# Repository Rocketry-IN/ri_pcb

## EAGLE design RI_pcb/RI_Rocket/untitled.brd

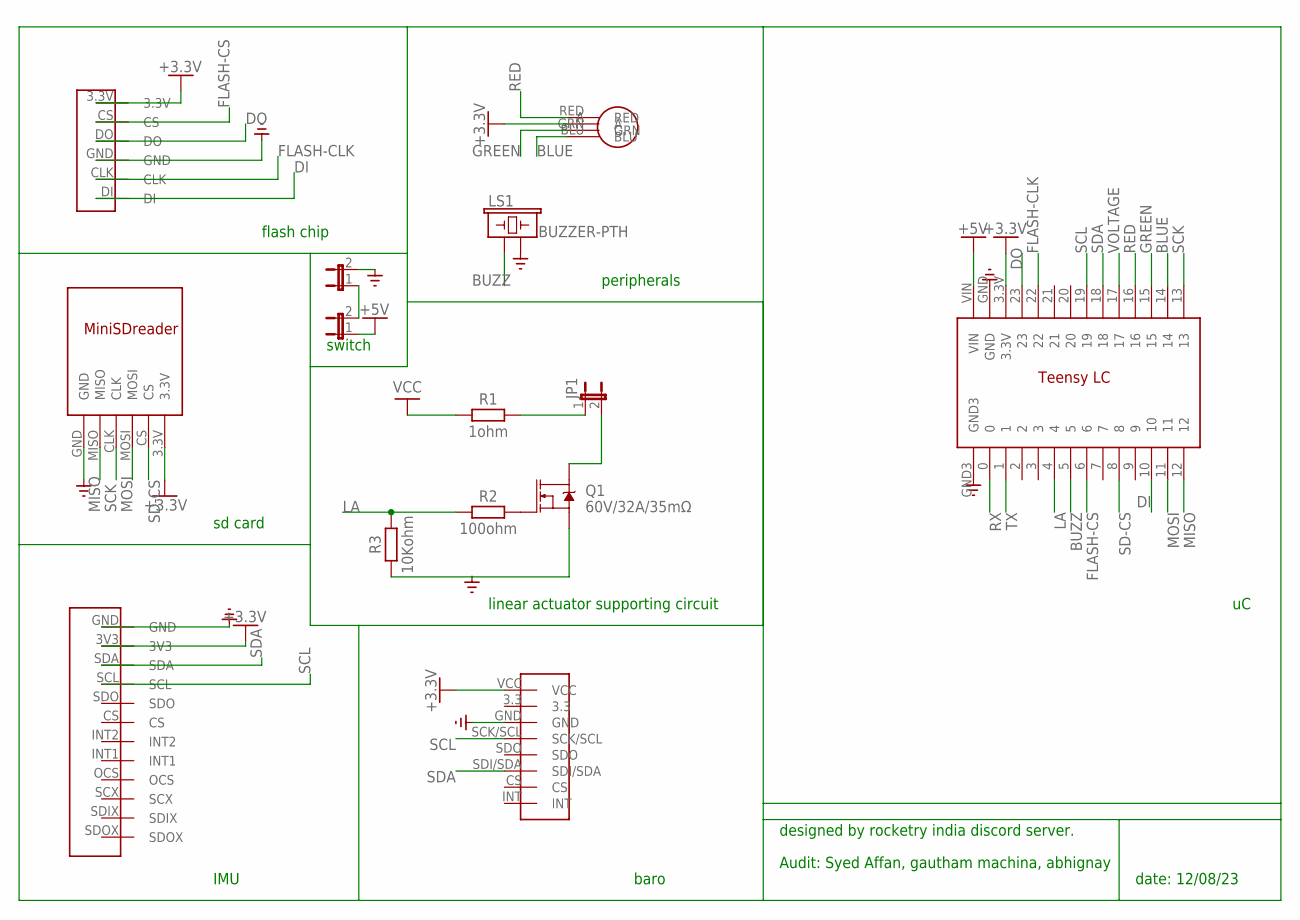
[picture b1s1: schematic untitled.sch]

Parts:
JP1, JP2, JP3: JP1E; JP1
LS1: BUZZER-PTH; BUZZER-12MM
Q1: 60V/32A/35mΩ; TO220V
R1: 1ohm; RESAD724W46L381D178B
R2: 100ohm; RESAD724W46L381D178B
R3: 10Kohm; RESAD724W46L381D178B
U$1: TEENSYLC
U$2: LED
U$3: FLASH
U$4: MINISDREADER
U$5: LSM6DSO
U$6: BMP390

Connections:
+3.3V: U$1.3.3V, U$2.A, U$3.3.3V, U$4.3.3V, U$5.3V3, U$6.VCC
+5V: JP3.1, U$1.VIN
BLUE: U$1.14, U$2.BLU
BUZZ: LS1.+ (1), U$1.5
DI: U$1.10, U$3.DI
DO: U$1.23, U$3.DO
FLASH-CLK: U$1.22, U$3.CLK
FLASH-CS: U$1.6, U$3.CS
GND: JP2.2, U$1.GND, U$3.GND, U$4.GND, U$5.GND, U$6.GND
GREEN: U$1.15, U$2.GRN
LA: R2.1, R3.2, U$1.4
MISO: U$1.12, U$4.MISO
MOSI: U$1.11, U$4.MOSI
unnamed: JP1.1, R1.2
unnamed: JP1.2, Q1.2 (D)
unnamed: Q1.1 (G), R2.2
unnamed: Q1.3 (S), R3.1
unnamed: JP2.1, JP3.2
RED: U$1.16, U$2.RED
RX: U$1.0
SCK: U$1.13, U$4.CLK
SCL: U$1.19, U$5.SCL, U$6.SCK/SCL
SD-CS: U$1.8, U$4.CS
SDA: U$1.18, U$5.SDA, U$6.SDI/SDA
TX: U$1.1
VCC: R1.1
VOLTAGE: U$1.17

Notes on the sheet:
designed by rocketry india discord server.
Audit: Syed Affan, gautham machina, abhignay
date: 12/08/23
switch
sd card
linear actuator supporting circuit
peripherals
IMU
baro
flash chip

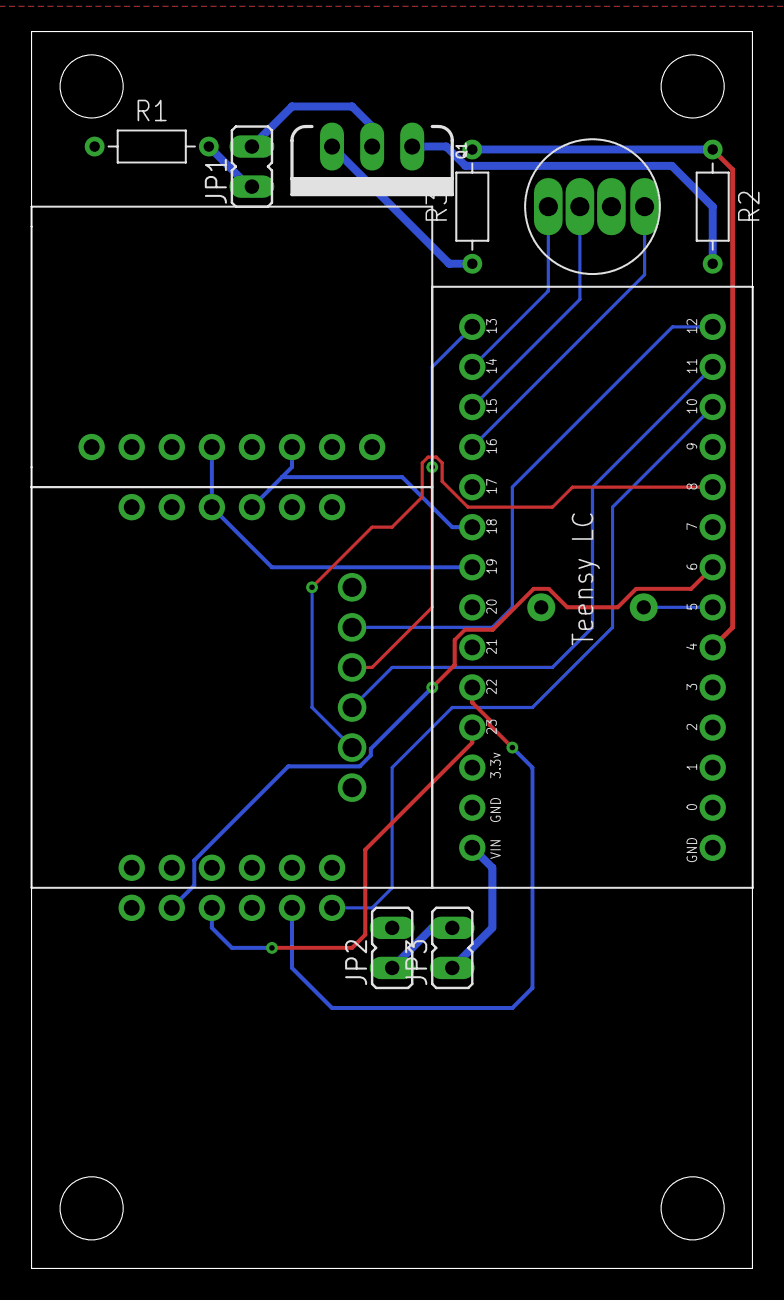
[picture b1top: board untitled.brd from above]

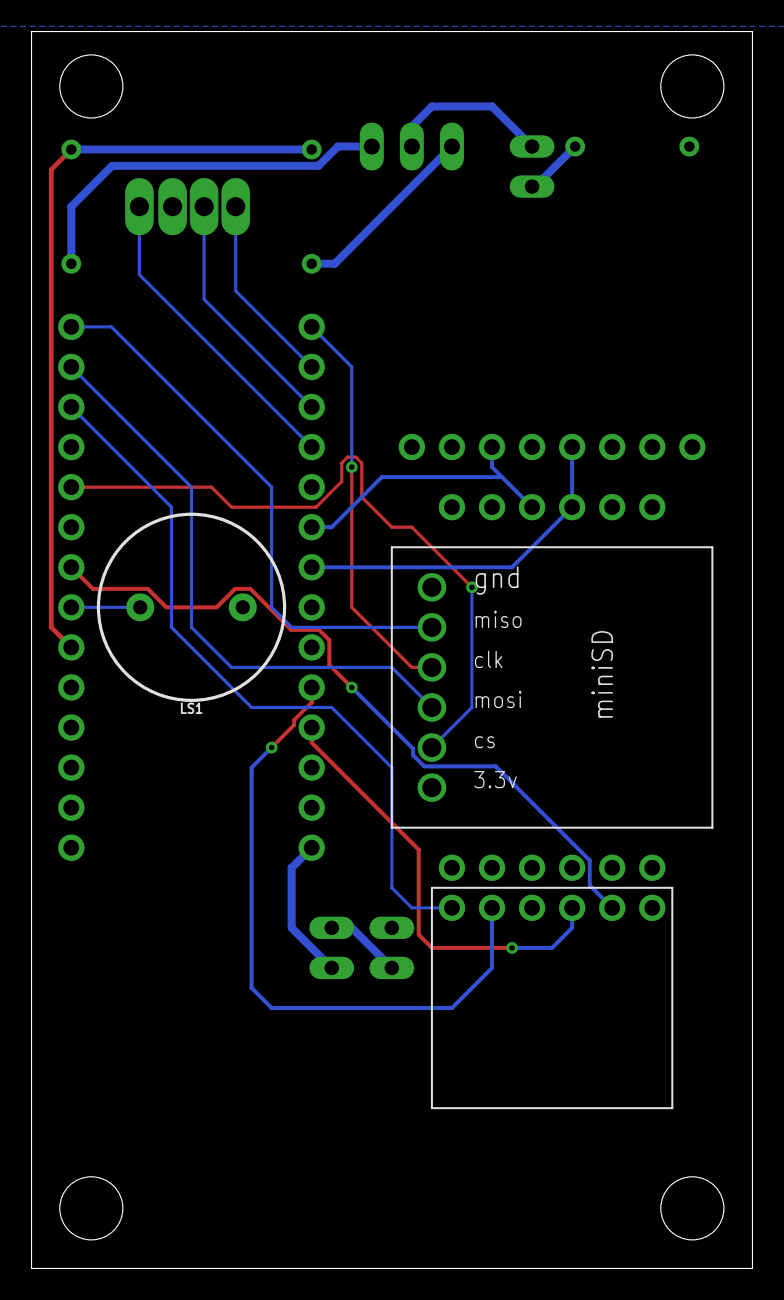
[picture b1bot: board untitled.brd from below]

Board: 2 copper layers, 45.7 x 78.4 mm, 14 parts (3 on the bottom side), 23 nets.

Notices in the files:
parts and their libraries:
SparkFun-Electromechanical: Licensing: Creative Commons ShareAlike 4.0 International - https://creativecommons.org/licenses/by-sa/4.0
